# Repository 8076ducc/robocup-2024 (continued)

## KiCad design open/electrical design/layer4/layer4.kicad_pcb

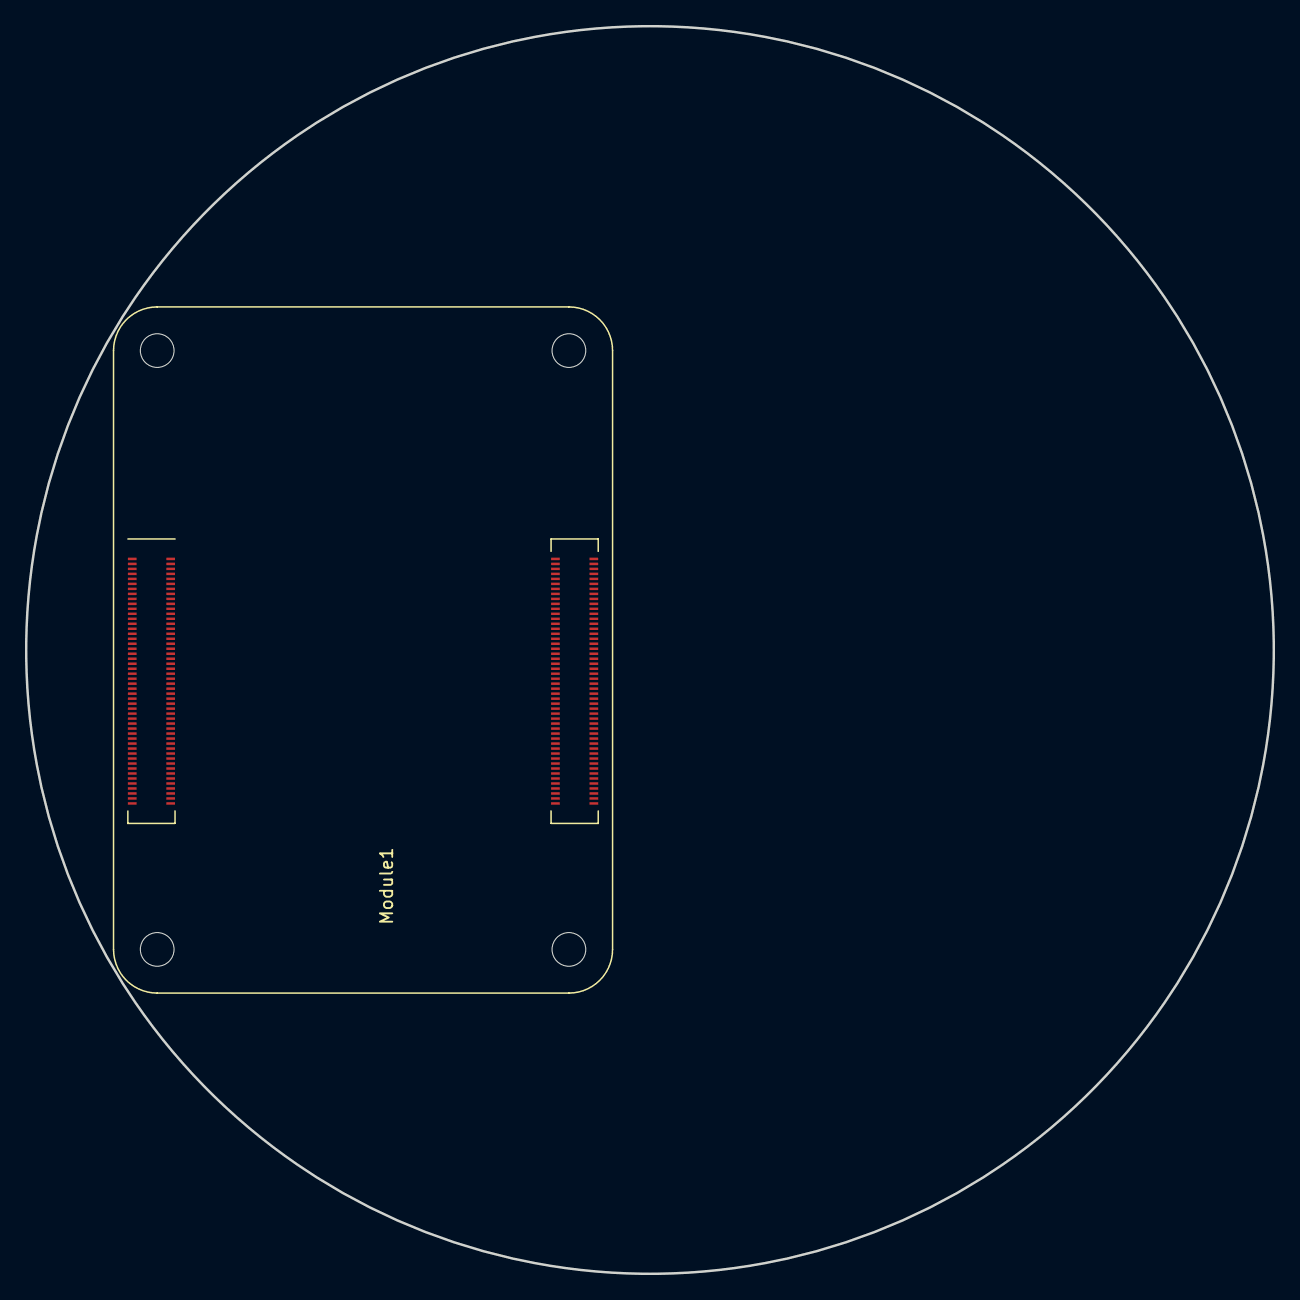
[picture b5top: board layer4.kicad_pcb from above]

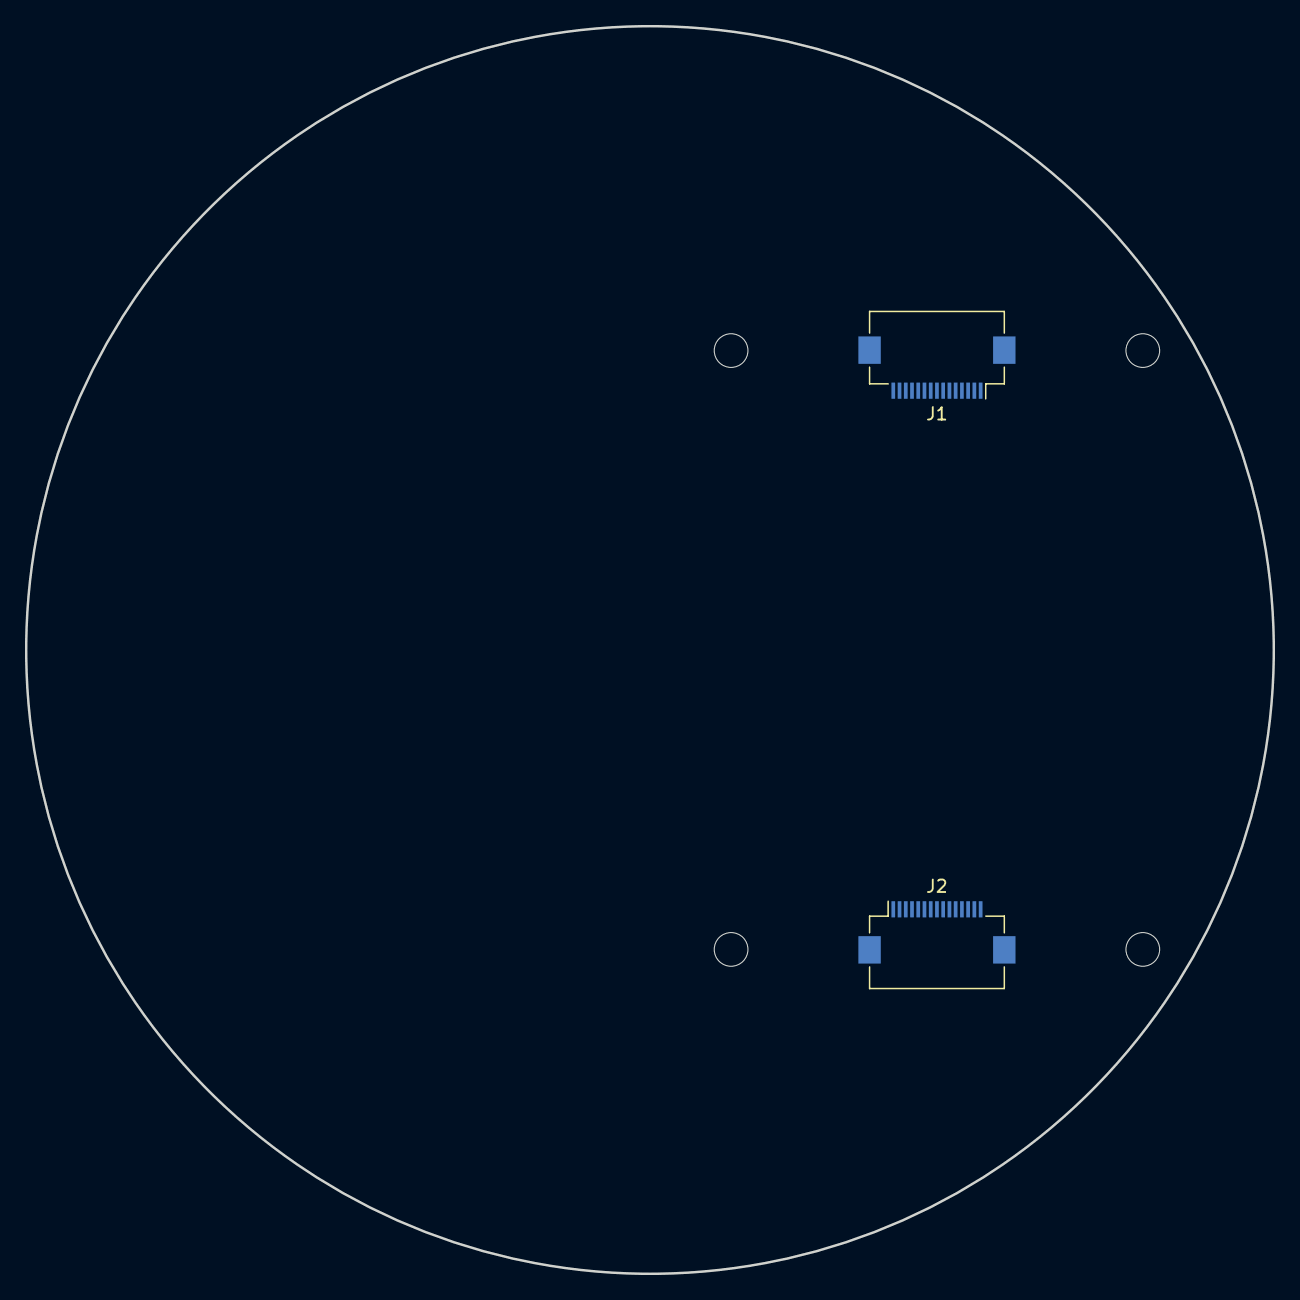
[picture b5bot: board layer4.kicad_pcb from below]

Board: 2 copper layers, 100.0 x 100.0 mm, 3 parts (2 on the bottom side), 20 nets, no tracks yet.

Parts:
J1, J2: Conn_01x15_Female; Hirose_FH12-15S-0.5SH_1x15-1MP_P0.50mm_Horizontal
Module1: ComputeModule4-CM4; Raspberry-Pi-4-Compute-Module

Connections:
+3V3: J1.15, J2.15, Module1.78 (GPIO_VREF(1.8v/3.3v_Input)), Module1.84 (+3.3v_(Output)), Module1.86 (+3.3v_(Output))
+5V: Module1.77 (+5v_(Input)), Module1.79 (+5v_(Input)), Module1.81 (+5v_(Input)), Module1.83 (+5v_(Input)), Module1.85 (+5v_(Input)), Module1.87 (+5v_(Input))
/rpi1/CAM0_C_N: J1.8, Module1.140 (CAM0_C_N)
/rpi1/CAM0_C_P: J1.9, Module1.142 (CAM0_C_P)
/rpi1/CAM0_D0_N: J1.2, Module1.128 (CAM0_D0_N)
/rpi1/CAM0_D0_P: J1.3, Module1.130 (CAM0_D0_P)
/rpi1/CAM0_D1_N: J1.5, Module1.134 (CAM0_D1_N)
/rpi1/CAM0_D1_P: J1.6, Module1.136 (CAM0_D1_P)
/rpi1/CAM1_C_N: J2.8, Module1.127 (CAM1_C_N)
/rpi1/CAM1_C_P: J2.9, Module1.129 (CAM1_C_P)
/rpi1/CAM1_D0_N: J2.2, Module1.115 (CAM1_D0_N)
/rpi1/CAM1_D0_P: J2.3, Module1.117 (CAM1_D0_P)
/rpi1/CAM1_D1_N: J2.5, Module1.121 (CAM1_D1_N)
/rpi1/CAM1_D1_P: J2.6, Module1.123 (CAM1_D1_P)
/rpi1/CAM_GPIO: J1.11, J2.11, Module1.97 (Camera_GPIO)
/rpi1/ID_SCL: J2.13, Module1.35 (ID_SC)
/rpi1/ID_SDA: J2.14, Module1.36 (ID_SD)
/rpi1/SCL0: J1.13, Module1.80 (SCL0)
/rpi1/SDA0: J1.14, Module1.82 (SDA0)
GND: J1.1, J1.4, J1.7, J1.10, J2.1, J2.4, J2.7, J2.10, Module1.1 (GND), Module1.2 (GND), Module1.7 (GND), Module1.8 (GND), Module1.13 (GND), Module1.14 (GND), Module1.22 (GND), Module1.23 (GND), Module1.32 (GND), Module1.33 (GND), Module1.42 (GND), Module1.43 (GND), Module1.52 (GND), Module1.53 (GND), Module1.59 (GND), Module1.60 (GND), Module1.65 (GND), Module1.66 (GND), Module1.71 (GND), Module1.74 (GND), Module1.98 (GND), Module1.107 (GND), Module1.108 (GND), Module1.113 (GND), Module1.114 (GND), Module1.119 (GND), Module1.120 (GND), Module1.125 (GND), Module1.126 (GND), Module1.131 (GND), Module1.132 (GND), Module1.137 (GND), Module1.138 (GND), Module1.144 (GND), Module1.150 (GND), Module1.155 (GND), Module1.156 (GND), Module1.161 (GND), Module1.162 (GND), Module1.167 (GND), Module1.168 (GND), Module1.173 (GND), Module1.174 (GND), Module1.179 (GND), Module1.180 (GND), Module1.185 (GND), Module1.186 (GND), Module1.191 (GND), Module1.192 (GND), Module1.197 (GND), Module1.198 (GND)

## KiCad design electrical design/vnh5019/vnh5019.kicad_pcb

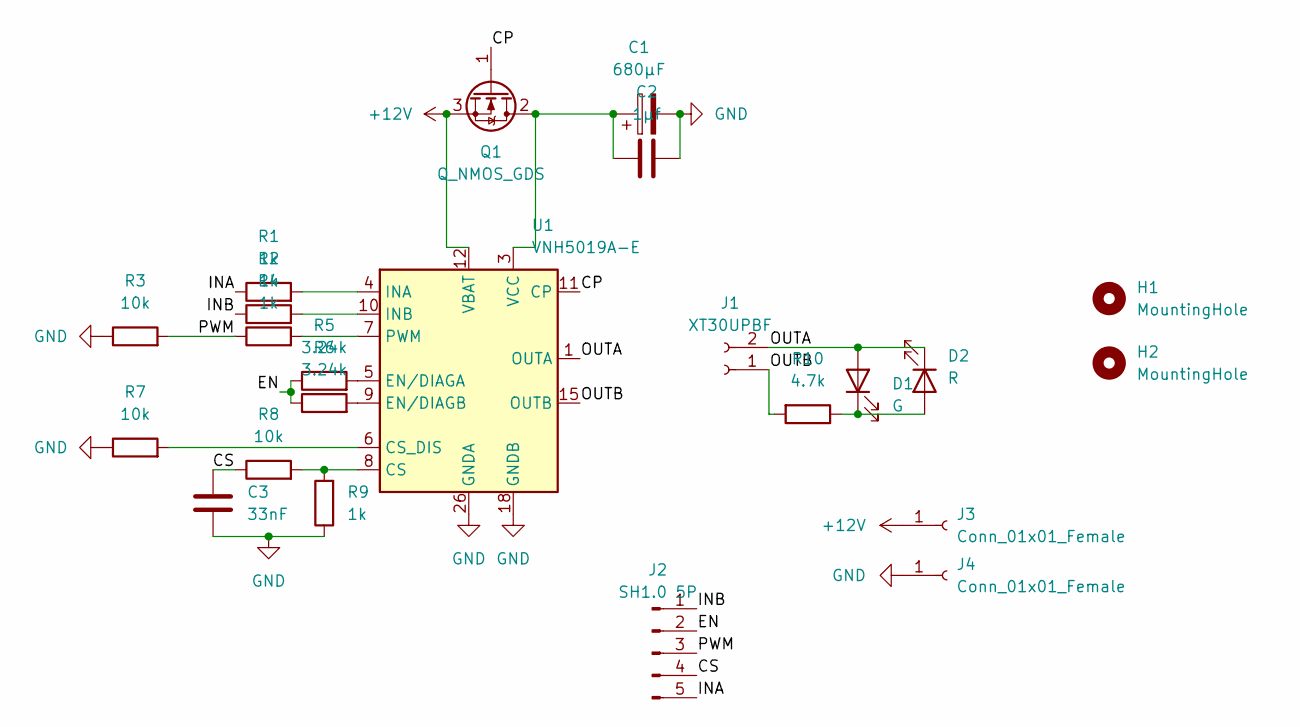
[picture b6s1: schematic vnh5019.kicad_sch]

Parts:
C1: 680µF; CP_Radial_D8.0mm_P3.50mm
C2: 1µf; C_0603_1608Metric
C3: 33nF; C_0603_1608Metric
D1: G; D_0603_1608Metric
D2: R; D_0603_1608Metric
H1, H2: MountingHole; MountingHole_3.2mm_M3_Pad
J1: XT30UPBF; AMASS_XT30UPB-F_1x02_P5.0mm_Vertical
J2: SH1.0 5P; JST_SH_SM05B-SRSS-TB_1x05-1MP_P1.00mm_Horizontal
J3, J4: Conn_01x01_Female; SolderWirePad_1x01_SMD_5x10mm
Q1: Q_NMOS_GDS; TO-252-2
R1, R2, R4, R9: 1k; R_0603_1608Metric
R3, R7, R8: 10k; R_0603_1608Metric
R5, R6: 3.24k; R_0603_1608Metric
R10: 4.7k; R_0603_1608Metric
U1: VNH5019A-E; ST_MultiPowerSO-30

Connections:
+12V: J3.1, Q1.3 (S), U1.12 (VBAT)
/CP: Q1.1 (G), U1.11 (CP)
/CS: C3.1, J2.4, R8.1
/EN: J2.2, R5.1, R6.1
/INA: J2.5, R1.1
/INB: J2.1, R2.1
/OUTA: D1.2 (A), D2.1 (K), J1.2, U1.1 (OUTA), U1.25 (OUTA), U1.30 (OUTA), U1.33 (OUTA)
/OUTB: J1.1, R10.2, U1.15 (OUTB), U1.16 (OUTB), U1.21 (OUTB), U1.32 (OUTB)
/PWM: J2.3, R3.2, R4.1
GND: C1.2, C2.2, C3.2, J4.1, R3.1, R7.1, R9.1, U1.18 (GNDB), U1.19 (GNDB), U1.20 (GNDB), U1.26 (GNDA), U1.27 (GNDA), U1.28 (GNDA)
unnamed: D1.1 (K), D2.2 (A), R10.1
unnamed: C1.1, C2.1, Q1.2 (D), U1.3 (VCC), U1.13 (VCC), U1.23 (VCC), U1.31 (VCC)
unnamed: R8.2, R9.2, U1.8 (CS)
unnamed: R7.2, U1.6 (CS_DIS)
unnamed: R5.2, U1.5 (EN/DIAGA)
unnamed: R6.2, U1.9 (EN/DIAGB)
unnamed: R1.2, U1.4 (INA)
unnamed: R2.2, U1.10 (INB)
unnamed: R4.2, U1.7 (PWM)

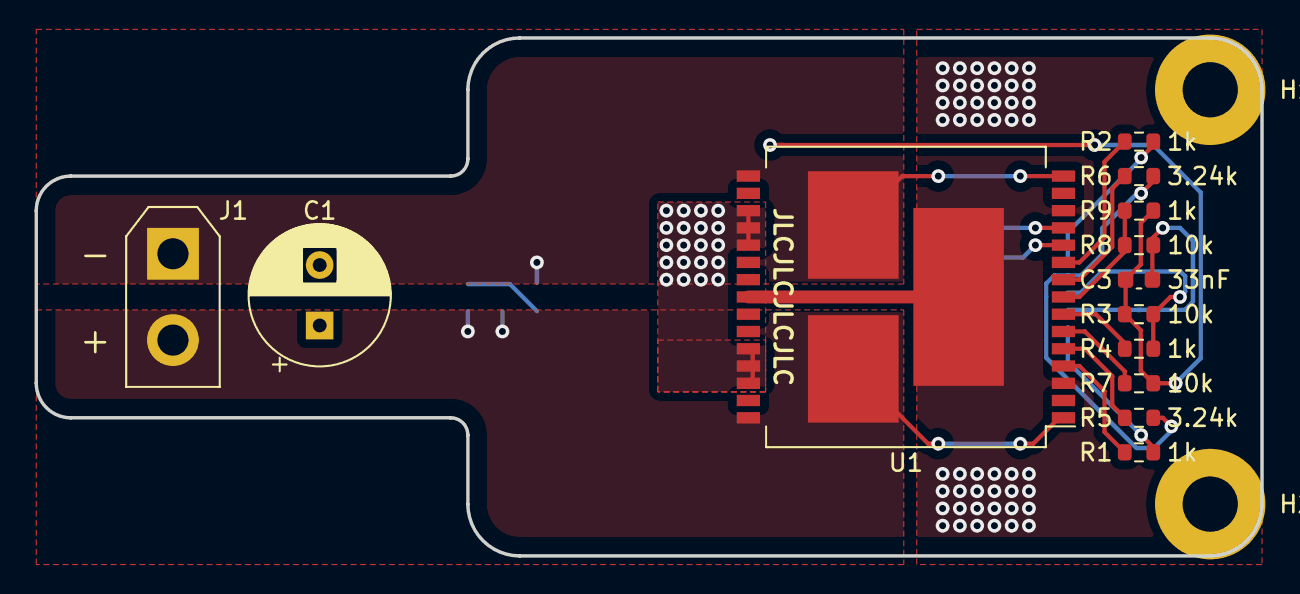
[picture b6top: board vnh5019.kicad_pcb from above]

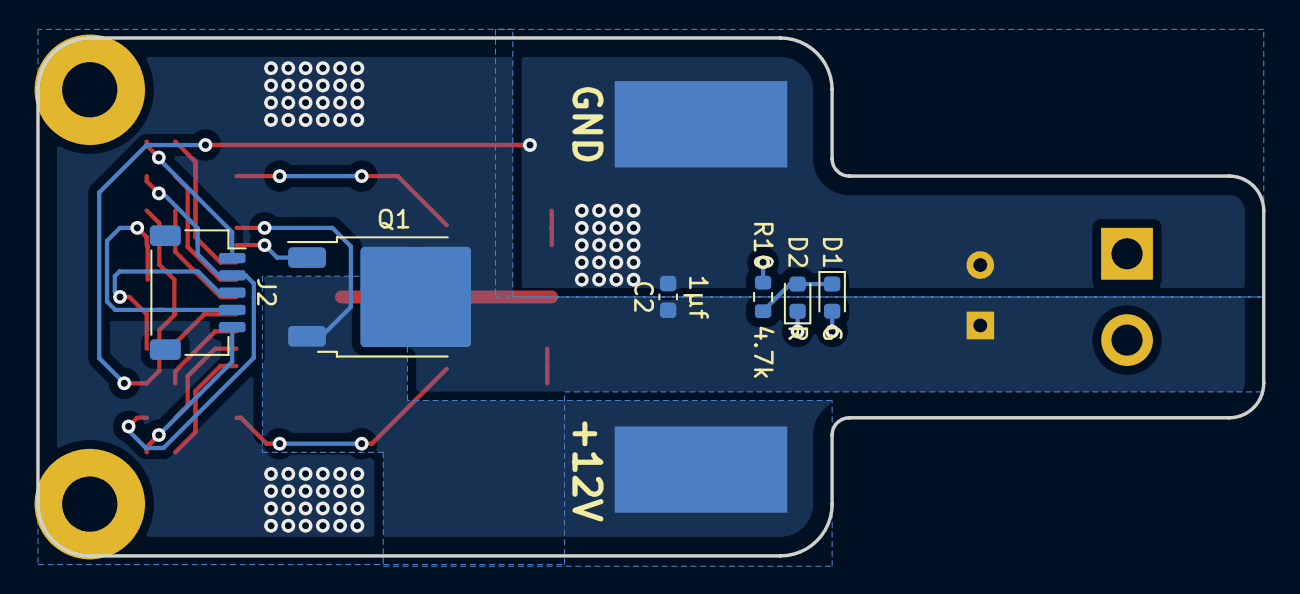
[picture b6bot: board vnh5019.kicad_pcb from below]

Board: 2 copper layers, 71.0 x 30.0 mm, 23 parts (8 on the bottom side), 19 nets.

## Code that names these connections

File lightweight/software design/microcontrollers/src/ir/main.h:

#pragma once
#ifndef _MAIN_H_
#define _MAIN_H_

#include <common.h>
#include <numeric>
#include <stm32f103c_variant_generic.h>
#include <movingAvg.h>

#define STM_LED PA3

extern STMTxDataUnion tx_data;

constexpr std::array<uint8_t, 24> IR_PINS = {
    PA2,
    PA1,
    PA0,
    PC15,
    PC14,
    PC13,
    PB9,
    PB8, 
    PB7,
    PB6,
    PB5,
    PB4,
    PB3,
    PA15,
    PA12,
    PA11,
    PB12, 
    PB15,
    PB14,
    PB0,
    PA7,
    PA6,
    PA5,
    PA4
};

#endif

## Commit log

2023-10-21 add git files
2023-10-21 add layer 1 shroud files
2023-10-21 add dribbler files
2023-10-21 add cycloidal gearbox files
2023-11-01 start work on layer 1 pcb
2023-11-01 add layer 2, 3, and 4 pcb files
2023-11-01 add omniwheel mesh files
2023-11-01 update dribbler mesh files
2023-11-01 update cycloidal drive mesh files
2023-11-01 add layer 1 drawings
2023-11-19 update layer 1 pcb
2023-11-19 update layer 2 pcb
2023-11-19 update layer 3 pcb
2023-11-19 update layer 4 pcb
2023-11-19 include new kicad libraries and vnh5019 pcb
2023-11-19 updated pcb plate drawings
2023-11-19 update pcb plate drawings
2023-11-20 placed layer 1 mounting holes
2023-11-20 placed layer 2 mth
2023-11-22 add boost to l1 pcb and update mech drawing
2023-11-22 routed l1 mux
2023-11-23 route l1 signal lines and resolve drc issues
2023-11-23 add XIAO and teensy footprint drawings
2023-11-23 update layer 1 pcb drawing
2023-11-23 update layer 2 pcb drawing
2023-11-24 reposition kicker circuit and improve routing
2023-12-14 change driver output connector to 5 pins
2023-12-14 update layer 1 design files
2023-12-14 add connectors for power transfer to l3
2023-12-14 lay out components on l3
2023-12-14 update pcbs and mech drawings
2023-12-15 mostly finalise pcb drawings for pre-fab
2023-12-15 update l2 pcb with additional batt connectors
2023-12-15 routed layer 3
2023-12-15 update pcbs for dual camera design
2023-12-16 add indicator leds to driver pcb
2023-12-16 change EN switch to larger one
2023-12-16 add fb between vccq and 3v3
2023-12-16 route layer 3
2023-12-16 add pwm pullup resistor to rpi fan connector
2023-12-16 add 5v test point on l3
2023-12-16 amend buck conv pinouts on l1 and l3
2023-12-17 update l3 pcb with new board outline
2023-12-17 reposition motor power ports
2023-12-17 resolve some l2 and l3 board issues
2023-12-17 add jlc order number silkscreen
2023-12-18 reroute 90 deg traces on l3 pcb
2023-12-18 add ducc finishes and route unconnected l3 items
2023-12-24 finalise pcbs for production
2023-12-24 start programming
2023-12-24 add second teensy code files
2023-12-24 update code (serial stopped working)
2023-12-25 get basic serial communication working
2023-12-25 add files for imu and bt µCs
2023-12-25 improve line detection and add calib method
2023-12-25 create robot, ball, and pose classes
2023-12-25 add dribbler and base setup
2023-12-25 remove packetserial and update debug baudrate
2023-12-28 organise files into 1 project and add packetserial
2024-01-01 correct led inductor value
2024-01-01 implement ema + serial and correct syntax errors
2024-01-02 correct reversed buck layout on l1 pcb
2024-01-07 update code
2024-01-07 add README
2024-01-11 mostly working line avoidance
2024-01-13 minimally working lidar localisation program
2024-01-16 layer 1 lw pcb
2024-01-17 moved boost cirvcuit on lw layer 1
2024-01-17 complete wall detection and intercept calc
2024-01-17 refactor code and improve regression model
2024-01-17 change regression for y-axis walls
2024-01-23 sstls
2024-01-24 reorg folders; added cura profile
2024-01-25 stl files for dribbler
2024-01-29 add new ender 3 v2 curaprofile
2024-01-29 reinstate kicad gitignore
2024-01-29 reinstate open elec files
2024-01-29 remove remnant elec files in parent folder
2024-01-29 update omniwheel files
2024-01-29 update shrouds
2024-01-30 stls
2024-01-31 updated layer 1
2024-02-01 add slicer files
2024-02-08 added layer 2
2024-02-19 remove elec files, update mech files, update code
2024-02-20 update lw pcbs
2024-02-20 fix layer 1 corrupted files; re-format folder
2024-02-20 move stuff around layer 3; add stm32 prog switch
2024-02-20 reposition ir ring
2024-02-21 updater layer 3
2024-02-21 add new dribbler moulds
2024-02-21 update lw l3 pcb
2024-02-21 resolve pcb merge conflicts
2024-02-22 fix drc faults on l1, l2, and l3 pcbs
2024-03-14 add working bt client and server code
2024-03-14 fix line approach angle calc
2024-03-14 update rest of code to pipe data via bluetooth
2024-03-14 refactor folder structure
2024-03-14 add cpp opencv tracking code
2024-03-14 add namespaces
2024-03-19 add lw pcb files
2024-03-19 add open mech drawings
2024-03-19 update camera and teensy code
2024-03-20 working basic ball track code
2024-03-23 upload
2024-03-25 working goalie program
2024-03-25 update cura config
2024-03-25 stl files
2024-03-27 migrate all the lidar stuff to t2; refine orbit
2024-03-28 port cam code from rpi to main repo
    finish kalman filtered, threaded opencv object tracking (1 core for lccv image pulling, 3 cores for ball and goal detection) + custom COBS-encoded serial output to teensy
2024-03-28 fix lidar transfer bugs, working orbit code
2024-03-28 port open code to lw
2024-03-31 dribbler stls new)
2024-04-01 thread teensy 2 lidar, add line tracking code
2024-04-01 mutex lock teensy threads
2024-04-04 stsl
2024-04-05 dxf handle
2024-04-05 5 apr code
2024-04-19 lightweight code
2024-05-06 rerouted lw l3 ir stm circuit
2024-05-06 layer 3 save
2024-08-02 WE'RE FREE
2025-02-01 remove pcb backup zip files
2025-02-01 update platformio gitignore
2025-02-01 update master gitignore and add .pio folders
2025-02-01 make rpi readme more comprehensive
2025-02-01 append more stuff to rpi readme
